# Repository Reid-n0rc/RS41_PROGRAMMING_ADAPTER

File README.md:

# RS41_PROGRAMMING_ADAPTER
 Adapter to go from STLink V2 Mini programmer to the RS41 programming header.

I created this adapter board to help with loading custom firmware from the https://github.com/MrARM/RS41ng project.

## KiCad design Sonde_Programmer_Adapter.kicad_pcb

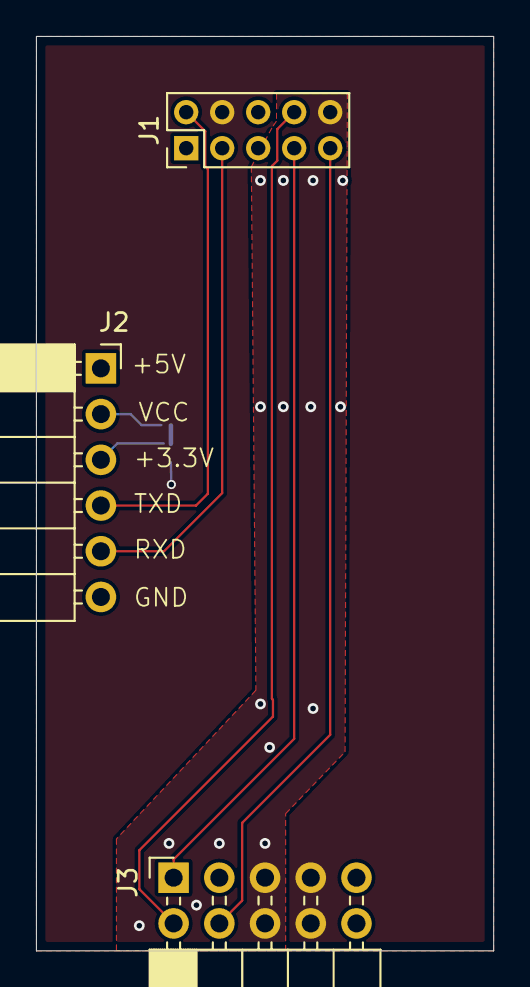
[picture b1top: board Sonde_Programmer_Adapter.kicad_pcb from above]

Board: 2 copper layers, 25.4 x 50.8 mm, 4 parts (1 on the bottom side), 9 nets.

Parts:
J1: RS41_CONN; PinHeader_2x05_P2.00mm_Vertical
J2: Conn_01x06; PinSocket_1x06_P2.54mm_Horizontal
J3: to programmer; PinSocket_2x05_P2.54mm_Horizontal
JP1: JUMPER-SMT_3_1-NC; SMT-JUMPER_3_1-NC_TRACE_NO-SILK

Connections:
+3.3V: J1.4, J3.7, J3.8, JP1.1
/I2C2_SCL/UART3_TX: J1.3, J2.5
/I2C2_SDA/UART3_RX: J1.2, J2.4
/RST: J1.7, J3.1
/SWCLK: J1.8, J3.2
/SWDIO: J1.9, J3.4
GND: J1.1, J1.10, J2.6, J3.5, J3.6
unnamed: J2.2, JP1.3
unnamed: J2.3, JP1.2

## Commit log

2024-03-10 complete adapt
2024-03-20 Update LICENSE
    Change license to CERN Open Hardware Licence Version 2 - Permissive
2024-03-20 Create LICENSE
